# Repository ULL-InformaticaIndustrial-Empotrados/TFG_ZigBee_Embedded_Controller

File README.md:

Trabajo de Fin de Grado
=======================

"Controlador central de domótica usando el protocolo de comunicación inalámbrico ZigBee"
----------------------------------------------------------------------------
**Autor: Enrique Hernández Bello**
**Tutor: Alberto Francisco Hamilton Castro**

#### Resumen

El *Internet de las Cosas* (IoT) es un concepto cada vez más familiar en nuestros hogares, fruto de conectar cada día, más y más dispositivos y electrodomésticos a la red de redes.

Con el auge cada vez más alto de dispositivos a interconectar, se hace necesario un sistema central que permita gestionarlos de forma flexible y eficiente.

Este proyecto lleva a cabo la confección de un sistema domótico de control remoto basado en tecnologías específicas, entre ellas, el protocolo de comunicación ZigBee.

Para su implementación, hace uso de módulos XBee integrando, además, otros diferentes componentes que aportan cada funcionalidad marcada como requisito.

Entre las muchas características de este proyecto, podemos destacar las siguientes:
* Es de filosofía libre y ha servido para contribuir a mejorar proyectos libres ya existentes.
* A destacar su diseño modular, que permite obtener las mejores características de cada componente y facilita la evolución del sistema intercambiándolos por otros equivalentes cuando sea necesario.
* Está pensado para ser distribuido en un Sistema Embebido, como es la PandaBoard.
* Ha sido diseñado para maximizar la flexibilidad en su configuración para adaptarse de la mejor forma a las necesidades del usuario.

**Palabras clave**: Domótica, IoT, XBee, ZigBee, PandaBoard, Ubuntu Core, Domoticz, Python, MQTT, Node-RED, Sensores, Actuadores.

###### 2016, Universidad de La Laguna

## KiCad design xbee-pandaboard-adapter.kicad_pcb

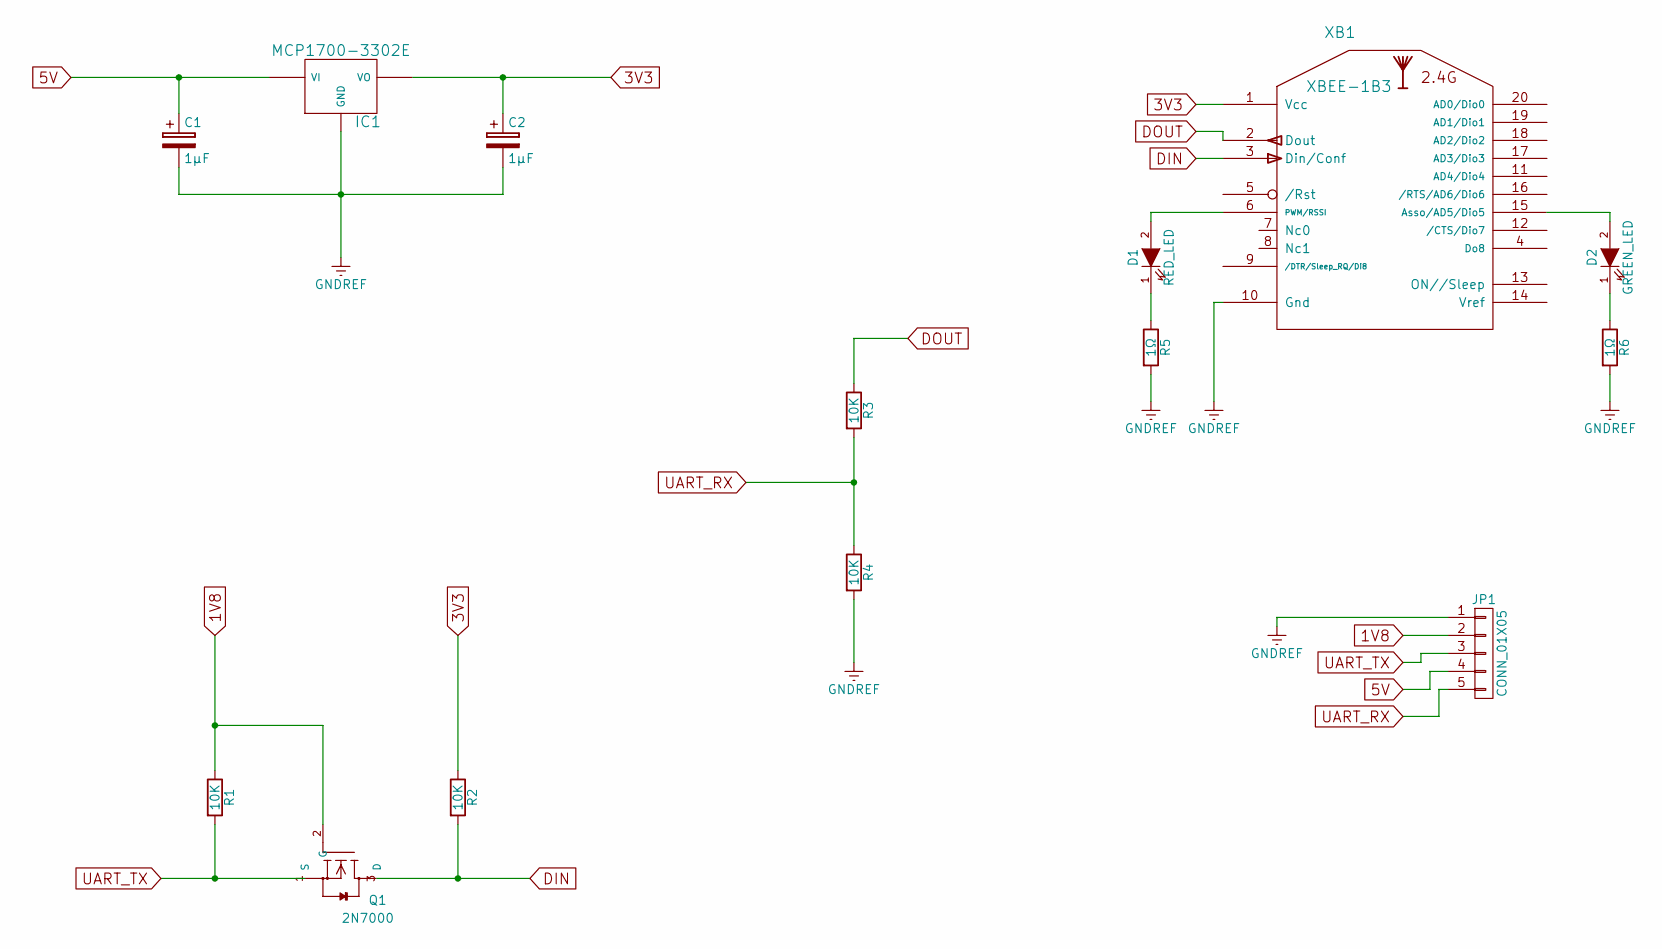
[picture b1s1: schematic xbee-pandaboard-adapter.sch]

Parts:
C1, C2: 1µF; C_Disc_D6_P5
D1: RED_LED; LED-3MM
D2: GREEN_LED; LED-3MM
IC1: MCP1700-3302E; TO-92_Inline_Narrow_Oval
JP1: CONN_01X05; Pin_Header_Angled_Inverted_1x05
Q1: 2N7000; TO-92_Inline_Narrow_Oval
R1, R2, R3, R4: 10K; Resistor_Horizontal_RM10mm
R5, R6: 1Ω; Resistor_Horizontal_RM10mm
XB1: XBEE-1B3; XBEE

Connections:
1V8: JP1.2, Q1.2 (G), R1.1
3V3: C2.1, IC1.3 (VO), R2.1, XB1.1 (Vcc)
5V: C1.1, IC1.2 (VI), JP1.4
DIN: Q1.3 (D), R2.2, XB1.3 (Din/Conf)
DOUT: R3.1, XB1.2 (Dout)
GNDREF: C1.2, C2.2, IC1.1 (GND), JP1.1, R4.2, R5.2, R6.2, XB1.10 (Gnd)
unnamed: D1.1 (K), R5.1
unnamed: D1.2 (A), XB1.6 (PWM/RSSI)
unnamed: D2.1 (K), R6.1
unnamed: D2.2 (A), XB1.15 (Asso/AD5/Dio5)
UART_RX: JP1.5, R3.2, R4.1
UART_TX: JP1.3, Q1.1 (S), R1.2

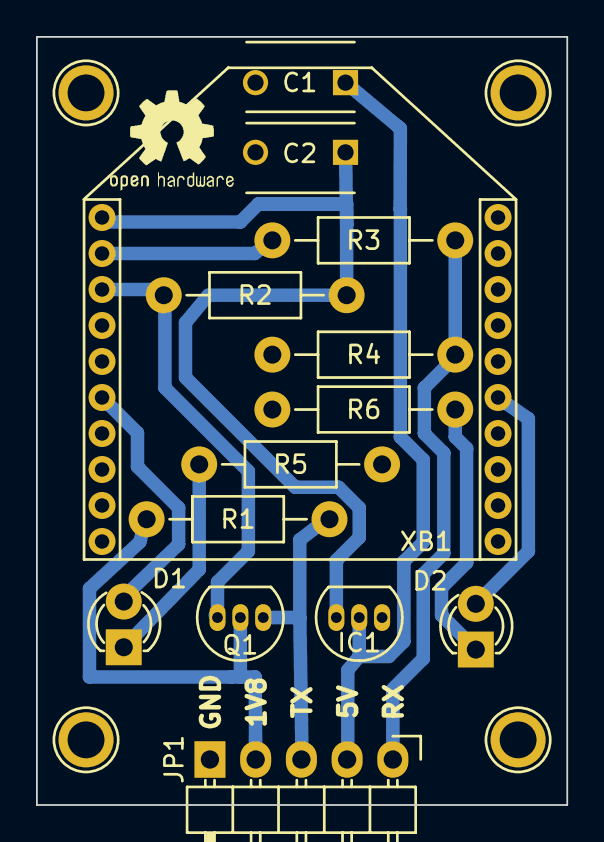
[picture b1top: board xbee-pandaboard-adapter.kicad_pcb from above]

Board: 2 copper layers, 29.5 x 42.7 mm, 14 parts (0 on the bottom side), 12 nets.

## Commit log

2015-04-29 Herramientas en Python para conectar con el coordinador
2015-04-29 Ingoramos los .pyc
2015-04-29 Ejemplo de pequeña aplicación para gestionar nodo remoto con pulsadores, leds y reles
2016-01-21 Mir server snap
2016-01-26 updated to snapcraft2.0
2016-01-26 use path
2016-02-03 final commit for Snapcraft2.0
2016-02-03 update for snapcraft2.1 skills
2016-02-03 Don't use PkgConfig, fix paths
2016-02-04 update for skills
2016-02-09 Fullscreen WM
2016-02-09 Add missing packages
2016-02-10 Add include path
2016-03-01 update to mir20
2016-03-10 Traemos últimas modificaciones
2016-03-10 update for plugs
2016-03-22 correct version in yaml
2016-04-08 update cmake paths
2016-04-27 update yaml with new interface
2016-05-02 update pathing
2016-07-06 update mir version and add strict
2016-07-19 Initial import.
2016-08-09 rely on opengl for relevant paths, mir interface PR reworked accordingly
2016-08-10 Initial release.
2016-08-11 Added missing bottom solder mask layer and others.
2016-08-26 Increased trace clearance and spoke width.
2016-08-27 Add specific MQTT devices with individual Device Topics
2016-08-27 Add 'createvirtualsensor' command to accept new devices from MQTT.
2016-08-27 Accepts input MQTT messages that include Device Topics
2016-08-29 Añadidos los perfiles de configuración de ambos XBee's.
2016-08-30 Shows TOPIC_OUT/TOPIC_IN as prefix for Device Topic in dialogs for MQTT sensors
2016-09-01 bump to mir0.24
2016-09-02 Fix creating custom MQTT device sensors from GUI.
2016-09-02 Fixed the modification of SensorUnit for Custom Sensor in Edit Device menu
2016-09-02 Fixed parsing topic of devices on incoming MQTT messages
2016-09-02 Fixed 'MQTT: Invalid data received!' message after the successful creation of devices.
2016-09-02 Fixed unknown device name in the device information sent by MQTT.
2016-09-02 Included the source command causes the sending of information from one device through MQTT.
2016-09-04 Updated README.md file
2016-09-04 Replaced obsolete 'copy' plugin by the new 'dump' plugin.
2016-09-04 Bump to kernel version v4.4.19
2016-09-04 Enabled CONFIG_FB_PRE_INIT_FB and CONFIG_FB_OMAP2 flags for UBoot splash support
2016-09-04 Enable CONFIG_RTC_DRV_TWL4030 flag to enable RTC on PandaBoard
2016-09-04 Added support for USB peripherals.
2016-09-04 Enabled the Display SubSystem for PandaBoard.
2016-09-07 update example server for mir0.24 buffer stream changes
2016-09-07 clean up arch and ld lib path
2016-09-10 Enabled AppArmor compatibility patches in kernel.
2016-09-10 Fixed snap grade to 'stable'
2016-09-11 Añadidos los ficheros de configuración para NodeRED y xbee2mqtt
2016-09-12 Revert "update example server for mir0.24 buffer stream changes"
    This reverts commit 9e43e3197d3c630f88b1a1f2182a091f141fd6eb.
2016-09-12 Downgrade version to 0.21 of mir in xenial.
2016-09-13 Añadido "model assertion" para la generación de la imagen resultante.
2016-09-13 Actualizado el fichero README.md.
2016-09-13 Añadido fichero BUILD.md con detalles actualizados de construcción
2016-09-16 Enable Bluetooth and RFKILL support for PandaBoard.
2016-09-21 Añadida la presentaión para la defensa del proyecto.
2022-10-24 Adding tarfile member sanitization to extractall()

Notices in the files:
xbee-pandaboard-adapter.kicad_pcb:
CERN Open Hardware License 1.1
